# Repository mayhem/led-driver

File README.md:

# led-driver

KiCAD schematics/board layout for a SCL2004 based LED driver

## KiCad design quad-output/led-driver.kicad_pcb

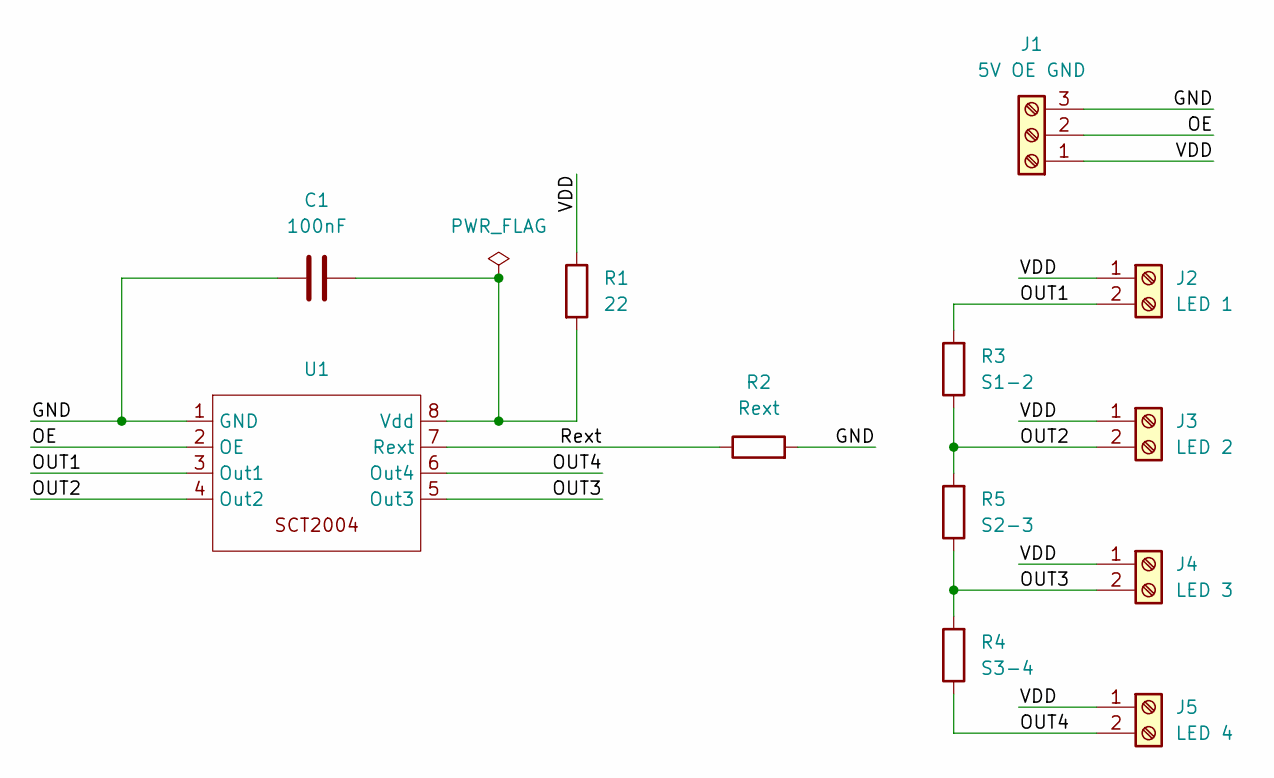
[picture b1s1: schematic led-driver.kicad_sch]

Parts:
C1: 100nF; C_0805_2012Metric_Pad1.18x1.45mm_HandSolder
J1: 5V OE GND; TerminalBlock_Phoenix_PT-1,5-3-3.5-H_1x03_P3.50mm_Horizontal
J2: LED 1; TerminalBlock_Phoenix_PT-1,5-2-3.5-H_1x02_P3.50mm_Horizontal
J3: LED 2; TerminalBlock_Phoenix_PT-1,5-2-3.5-H_1x02_P3.50mm_Horizontal
J4: LED 3; TerminalBlock_Phoenix_PT-1,5-2-3.5-H_1x02_P3.50mm_Horizontal
J5: LED 4; TerminalBlock_Phoenix_PT-1,5-2-3.5-H_1x02_P3.50mm_Horizontal
R1: 22; R_0805_2012Metric_Pad1.20x1.40mm_HandSolder
R2: Rext; R_0805_2012Metric_Pad1.20x1.40mm_HandSolder
R3: S1-2; SolderJumper-2_P1.3mm_Open_Pad1.0x1.5mm
R4: S3-4; SolderJumper-2_P1.3mm_Open_Pad1.0x1.5mm
R5: S2-3; SolderJumper-2_P1.3mm_Open_Pad1.0x1.5mm
U1: SOP-8_3.76x4.96mm_P1.27mm

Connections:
/GND: C1.1, J1.3, R2.2, U1.1 (GND)
/OE: J1.2, U1.2 (OE)
/OUT1: J2.2, R3.2, U1.3 (Out1)
/OUT2: J3.2, R3.1, R5.2, U1.4 (Out2)
/OUT3: J4.2, R4.2, R5.1, U1.5 (Out3)
/OUT4: J5.2, R4.1, U1.6 (Out4)
/Rext: R2.1, U1.7 (Rext)
/VDD: J1.1, J2.1, J3.1, J4.1, J5.1, R1.1
unnamed: C1.2, R1.2, U1.8 (Vdd)

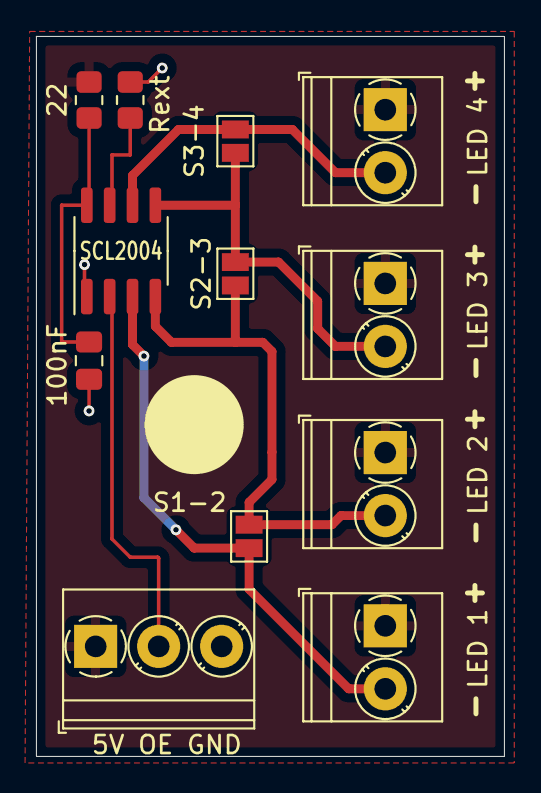
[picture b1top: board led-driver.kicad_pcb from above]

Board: 2 copper layers, 26.0 x 40.0 mm, 12 parts (0 on the bottom side), 9 nets.

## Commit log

2023-09-21 First post
